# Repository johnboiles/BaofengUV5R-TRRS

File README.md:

Baofeng UV5R TRRS Adapter
=========================
http://github.com/johnboiles/BaofengUV5R-TRRS

A tiny board, which allows a smartphone or similiar device to connect to the Baofeng UV5R radio via a [TRRS audio connector](https://en.wikipedia.org/wiki/Phone_connector_%28audio%29#TRRS_standards). It allows for connecting the radio to a software [TNC](https://en.wikipedia.org/wiki/Terminal_node_controller) app such as [APRSDroid](http://aprsdroid.org/) or [PocketPacket](https://itunes.apple.com/us/app/pocketpacket/id336500866?mt=8). Solder on the components, solder on the cables, then provide some stress relief, (I use solid-core wire and heat shrink tubing), and you can use your UV5R with your smartphone for APRS on the cheap.

Pictures
--------

Notes
-----
A small capacitor and 3 resistors to trick the iPhone into thinking a microphone was connected. This part of the schematic was inspired by [this article](http://www.creativedistraction.com/demos/sensor-data-to-iphone-through-the-headphone-jack-using-arduino/) on connecting Arduino to an iPhone.

A small capacitor on the speaker out of the radio removes any DC bias. (I'm not sure why this was necessary, but in my testing it made receipt of packets much more reliable.)

A 100Ω resistor is employed to improve detection on a variety of Android phones.

On my UV5R+, volume is maxed, vox is set to 2 and, squelch is set to 1. On my iPhone volume is also maxed.

Schematic
---------

Bill of Materials
-----------------
| Qty | Part                                                                                                 | Notes                                   |
|-----|------------------------------------------------------------------------------------------------------|-----------------------------------------|
| 1   | [Kenwood Type Speaker Mic Cable](https://www.argentdata.com/catalog/product_info.php?products_id=70) | You can also use 2.5mm and 3.5mm cable. |
| 1   | [3.5mm TRRS Cable](http://amzn.com/B00FJEGXLW)                                                       |                                         |
| 1   | 10kΩ Resistor 0603                                                                                   |                                         |
| 2   | 2.2kΩ Resistor 0603                                                                                  |                                         |
| 1   | 0.1kΩ Resistor 0603                                                                                  |                                         |
| 2   | 0.01uF Capacitor 0603                                                                                |                                         |
| 1   | 3" of 0.25" Diameter Heat Shrink Tubing                                                              | Optional                                |

How to Order
------------
You can order the board directly through [OSHPark](http://oshpark.com/shared_projects/qy523INb) ($1.70 for 3 boards with free shipping). Digikey or Mouser are good places to buy the resistors and capacitors.

Thanks
------

The following people have provided contributions to this design

* [kronicd VK6HAX](https://github.com/kronicd/) - optimisations to improve detection on a number of phones

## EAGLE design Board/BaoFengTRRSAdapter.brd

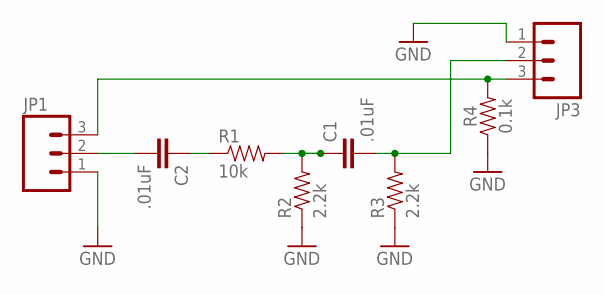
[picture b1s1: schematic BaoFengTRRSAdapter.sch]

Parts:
C1, C2: .01uF; 0603-CAP
JP1, JP3: M031X03_NO_SILK; 1X03_NO_SILK
R1: 10k; 0603-RES
R2, R3: 2.2k; 0603-RES
R4: 0.1k; 0603-RES

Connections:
BAOFENGMIC+: JP1.3, JP3.3, R4.2
GND: JP1.1, JP3.1, R2.1, R3.1, R4.1
unnamed: C2.2, JP1.2
unnamed: C1.1, R1.2, R2.2
unnamed: C1.2, JP3.2, R3.2
unnamed: C2.1, R1.1

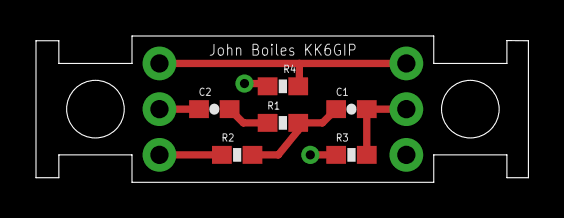
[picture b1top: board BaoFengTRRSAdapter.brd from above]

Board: 2 copper layers, 27.4 x 8.1 mm, 8 parts (0 on the bottom side), 6 nets.

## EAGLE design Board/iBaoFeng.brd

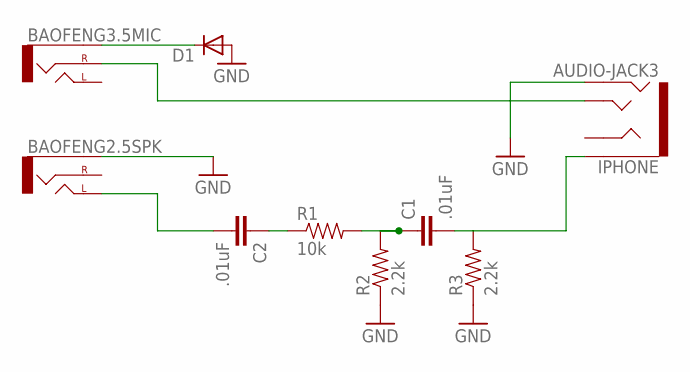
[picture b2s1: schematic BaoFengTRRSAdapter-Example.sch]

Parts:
BAOFENG2.5SPK: AUDIO-JACK2.5MM; STEREOJACK2.5MM_STEREOJACK2.5MM
BAOFENG3.5MIC: AUDIO-JACKHOLESONLY; STEREOJACK2.5MM_SPECIAL_HOLES-ONLY
C1, C2: .01uF; 0603-CAP
D1: DIODE1N4148; DIODE-1N4148
IPHONE: AUDIO-JACK3; AUDIO-JACK-TRRS-SMD
R1: 10k; 0603-RES
R2, R3: 2.2k; 0603-RES

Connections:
BAOFENGMIC+: BAOFENG3.5MIC.TIP (RIGHT), IPHONE.TIP
BAOFENGMIC-: BAOFENG3.5MIC.RING1 (SLEEVE), D1.C
BAOFENGSPK+: BAOFENG2.5SPK.SHIELD (LEFT), C2.2
GND: BAOFENG2.5SPK.RING1 (SLEEVE), D1.A, IPHONE.RING2, R2.1, R3.1
unnamed: C1.1, R1.2, R2.2
unnamed: C1.2, IPHONE.EARTH, R3.2
unnamed: C2.1, R1.1

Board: 2 copper layers, 9 parts (0 on the bottom side), 7 nets, no tracks yet.

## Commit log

2013-09-07 Full schematic of the board with audio jacks
2013-09-11 Changed from audio jacks to headers
2013-09-11 Renaming files, adding README and LICENSE
2013-10-12 Removing unnecessary diode, making board a bit smaller
2013-10-28 Updating readme and untenting vias. Including a version of the schematic that uses audio jacks.
2014-01-22 Adding a ground plane as per suggestion by Chris Hood (KE5SBP)
2014-01-22 Updating README with r3 board
2014-01-24 Adding OSHPark order info to README
2014-02-14 Adding photos to README
2016-04-20 Update README.md
    Tweaked text of README.md. Turned parts list into a markdown table.
2016-09-13 Fixed typo in resistors
2022-06-09 update to improve detection on various phones
2022-06-09 update to improve detection on various phones (#19)

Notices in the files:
parts and their libraries:
SparkFun-Connectors: Licensing: CC v3.0 Share-Alike You are welcome to use this library for commercial purposes.
SparkFun-Resistors: Licensing: Creative Commons ShareAlike 4.0 International - https://creativecommons.org/licenses/by-sa/4.0
